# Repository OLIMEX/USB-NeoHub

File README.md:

# USB-NeoHub
USB 1.1 and USB 2.0 compliant hub compatible with RP2040 PICO USB and TinyUSB allowing keyboard, USB Flash and other peripherals to be used together

## Features

* USB 1.1 and USB 2.0 compatible
* USB-C input
* USB-A x4 output
* Input power status LED
* Output power status LED
* current protection
* Industrial grade temperature range: -40+85℃
* Dimensions 46x34 mm

## Licenses

* Hardware is released under CERN Open Hardware Licence Version 2 - Strongly Reciprocal, all silkscreen credits to Olimex should remain;
* Software is released under GPL3 Licensee
* Documentation is released under CC BY-SA 4.0

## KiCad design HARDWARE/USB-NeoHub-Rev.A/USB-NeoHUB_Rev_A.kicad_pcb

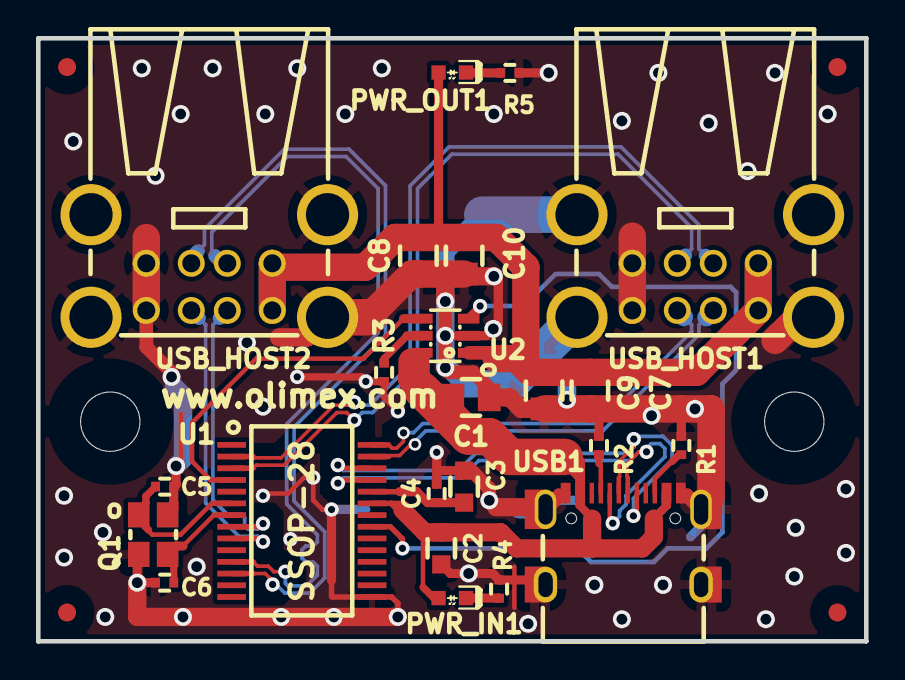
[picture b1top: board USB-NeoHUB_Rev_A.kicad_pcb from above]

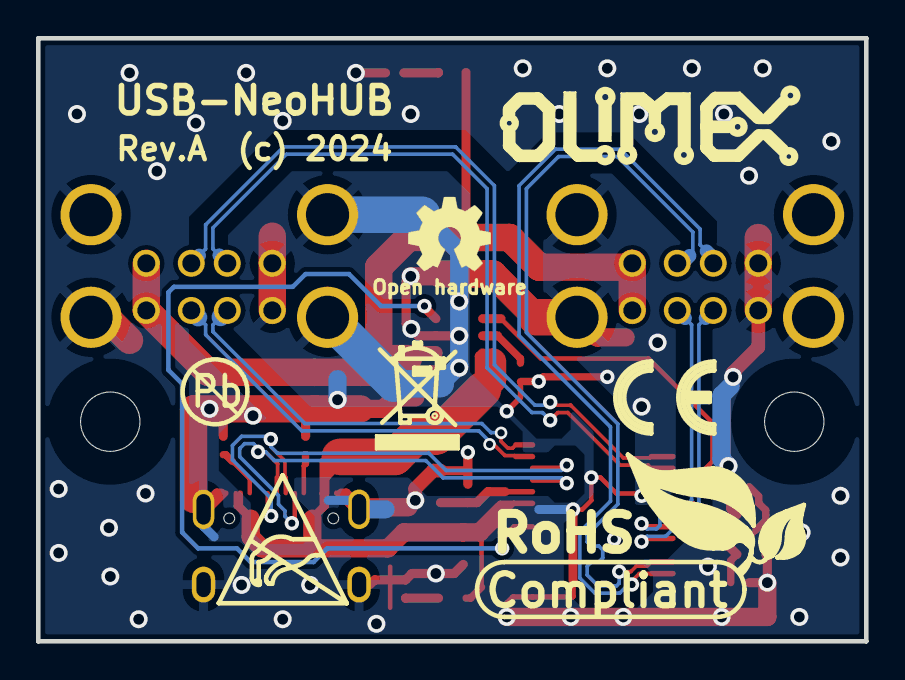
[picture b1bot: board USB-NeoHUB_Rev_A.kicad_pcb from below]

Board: 2 copper layers, 46.0 x 33.5 mm, 36 parts (7 on the bottom side), 23 nets.

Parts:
C1, C9, C10: 47uF/6.3V/20%/X5R/C0805; C_0805_5MIL_DWS
C2: 1uF/10V/20%/X5R/C0603; C_0603_5MIL_DWS
C3: 10uF/6.3V/20%/X5R/C0603; C_0603_5MIL_DWS
C4: 100nF/10V/10%/X7R/C0402; C_0402_5MIL_DWS
C5, C6: NA(27pF/50V/5%/C0G/C0402); C_0402_5MIL_DWS
C7, C8: NA(47uF/6.3V/20%/X5R/C0805); C_0805_5MIL_DWS
FID1, FID2: Fiducial; Fiducial1x3
FID3, FID4: Fiducial; Fiducial1x3_Paste
Logo_OLIMEX_TB: Logo_OLIMEX_TB
MH1, MH2: Mounting_Hole_NPTH; Mounting_Hole_Drill-3.3mm_Clerance-7mm
PWR_IN1: LED/GREEN/0603; LED_0603_KA
PWR_OUT1: LED/GREEN/0603; LED_0603_KA
Q1: Q12MHz/20pF/10ppm/4P/3.2x2.5mm; TSX-3.2x2.5mm_GND(3)
R1, R2, R4, R5: 5.1k/1%/R0402; R_0402_5MIL_DWS
R3: 30.1k/1%/R0402; R_0402_5MIL_DWS
Sign_Antistatic: Sign_Antistatic
Sign_CE: CE_Sign
Sign_OSHW_7.3x6.0mm: Sign_OSHW_7.3x6.0mm; Sign_OSHW_7.3x6.0mmn
Sign_PB-Free: Sign_PB-Free
Sign_RecycleBin_1: Sign_RecycleBin_1
Sign_RoHS_1: Sign_RoHS_1
U1: CH334S(SSOP-28); SSOP28
U2: CH217K(SOT23-6L); SOT23-6
USB1: USB-C-16P-F(A40-00119-A52-12); USB2.0_TYPE-C(A40-00119-A52-12)_Paste
USB_HOST1, USB_HOST2: USBB1-FRWH-4A(USB-Ax2); USB_TWO_LEVEL

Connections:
+5V_USB: C1.1, C2.1, PWR_IN1.2 (A), U1.23 (V5), U2.6 (VIN), USB1.A4 (VBUS), USB1.A9 (VBUS), USB1.B4 (VBUS), USB1.B9 (VBUS)
/+5V_USB_HOST: C7.2, C8.2, C9.2, C10.2, PWR_OUT1.2 (A), U2.1 (VOUT), USB_HOST1.1.1, USB_HOST1.2.1, USB_HOST2.1.1, USB_HOST2.2.1
/OVCUR#: U1.21 (OVCUR#), U2.3 (FLAG#)
/PWREN#: U1.4 (PWREN#), U2.4 (EN#)
/USB_D1+: U1.28 (DP1), USB_HOST1.1.3
/USB_D1-: U1.27 (DM1), USB_HOST1.1.2
/USB_D2+: U1.3 (DP2), USB_HOST1.2.3
/USB_D2-: U1.2 (DM2), USB_HOST1.2.2
/USB_D3+: U1.9 (DP3), USB_HOST2.1.3
/USB_D3-: U1.8 (DM3), USB_HOST2.1.2
/USB_D4+: U1.12 (DP4), USB_HOST2.2.3
/USB_D4-: U1.11 (DM4), USB_HOST2.2.2
/USB_D+: U1.26 (DPU), USB1.A6 (DP1), USB1.B6 (DP2)
/USB_D-: U1.25 (DMU), USB1.A7 (DN1), USB1.B7 (DN2)
GND: C1.2, C2.2, C3.2, C4.2, C5.2, C6.2, C7.1, C8.1, C9.1, C10.1, Q1.3 (case), R1.1, R2.1, R3.1, R4.2, R5.2, U1.15 (GND), U2.2 (GND), USB1.0 (SHELL), USB1.A1 (GND), USB1.A12 (GND), USB1.B1 (GND), USB1.B12 (GND), USB_HOST1.0, USB_HOST1.1.4, USB_HOST1.2.4, USB_HOST2.0, USB_HOST2.1.4, USB_HOST2.2.4
unnamed: PWR_IN1.1 (K), R4.1
unnamed: PWR_OUT1.1 (K), R5.1
unnamed: C3.1, C4.1, U1.24 (VDD33)
unnamed: C5.1, Q1.1, U1.6 (XI)
unnamed: C6.1, Q1.2, U1.7 (XO)
unnamed: R3.2, U2.5 (ISET)
unnamed: R2.2, USB1.A5 (CC1)
unnamed: R1.2, USB1.B5 (CC2)

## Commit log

2024-02-16 initial upload

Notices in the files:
HARDWARE/USB-NeoHub-Rev.A/USB-NeoHUB_Rev_A.kicad_pcb:
(c) 2024
